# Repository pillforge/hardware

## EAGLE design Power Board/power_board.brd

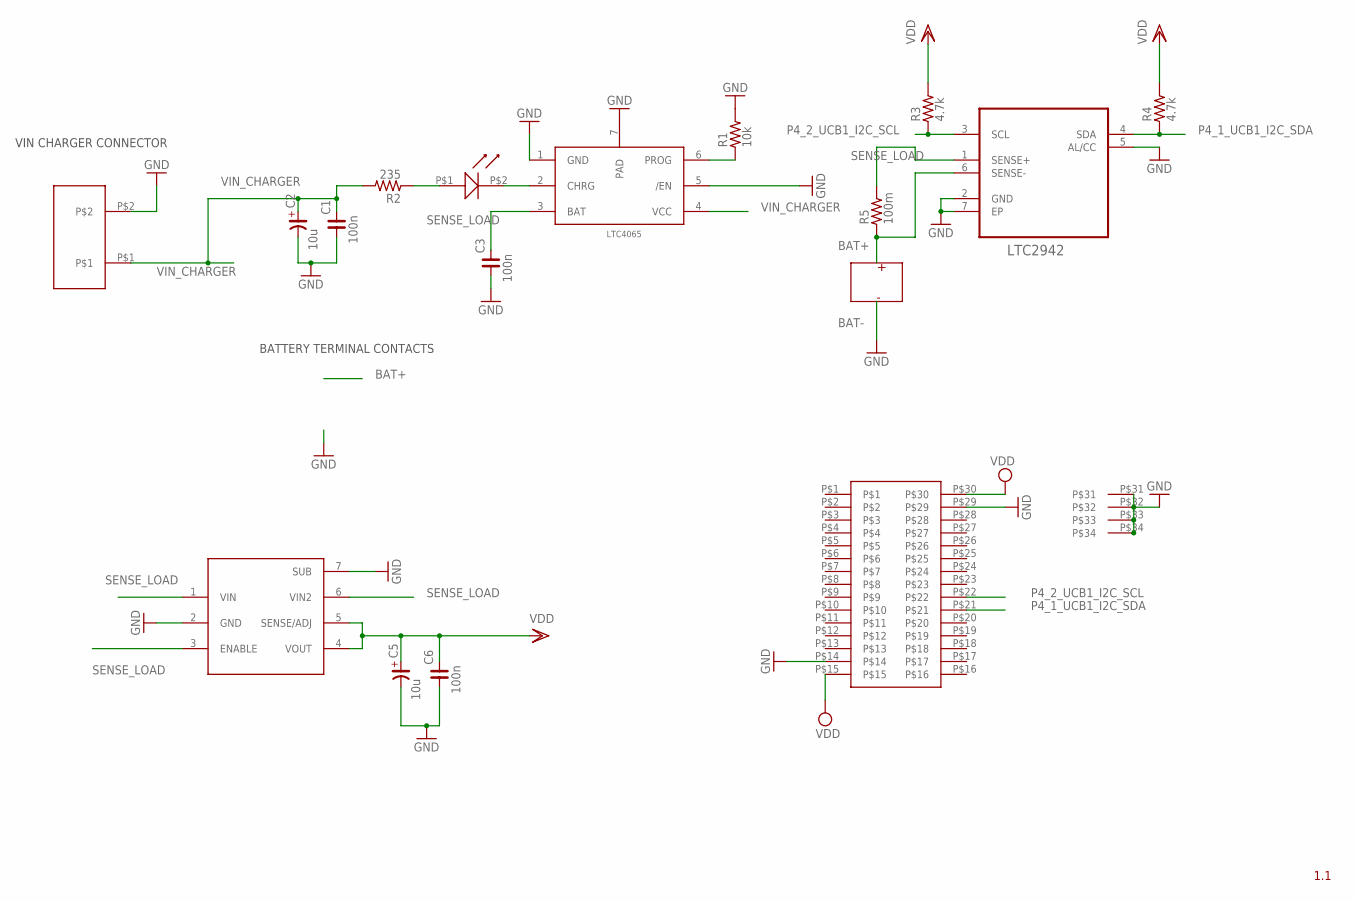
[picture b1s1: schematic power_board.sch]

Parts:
C1, C3, C6: 100n; C0402
C2, C5: 10u; C0402
R1: 10k; R0402
R2: 235; R0402
R3, R4: 4.7k; R0402
R5: 100m; R0402
U1: LTC2942CDCBTRMPBF; DFN200X300X80-7N
U$1: LTC4065
U$2: LED0402; LED_0402
U$3: 55909-0374_PLUG
U$4: NCP606
U$5: ASR_2_REC; ASR_2_CONN

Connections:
BAT+: R5.1, U1.6 (SENSE-)
GND: C1.1, C2.2 (-), C3.1, C5.2 (-), C6.1, R1.2, U1.2 (GND), U1.5 (AL/CC), U1.7 (EP), U$1.1 (GND), U$1.5 (/EN), U$1.7 (PAD), U$3.P$14, U$3.P$29, U$3.P$31, U$3.P$32, U$3.P$33, U$3.P$34, U$4.2 (GND), U$4.7 (SUB), U$5.P$2
unnamed: R1.1, U$1.6 (PROG)
unnamed: R2.1, U$2.P$1 (A)
unnamed: U$1.2 (CHRG), U$2.P$2 (K)
P4_1_UCB1_I2C_SDA: R4.1, U1.4 (SDA), U$3.P$21
P4_2_UCB1_I2C_SCL: R3.1, U1.3 (SCL), U$3.P$22
SENSE_LOAD: C3.2, R5.2, U1.1 (SENSE+), U$1.3 (BAT), U$4.1 (VIN), U$4.3 (ENABLE), U$4.6 (VIN2)
VDD: C5.1 (+), C6.2, R3.2, R4.2, U$3.P$15, U$3.P$30, U$4.4 (VOUT), U$4.5 (SENSE/ADJ)
VIN_CHARGER: C1.2, C2.1 (+), R2.2, U$1.4 (VCC), U$5.P$1

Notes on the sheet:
BAT-
BATTERY TERMINAL CONTACTS
VIN CHARGER CONNECTOR
1.1

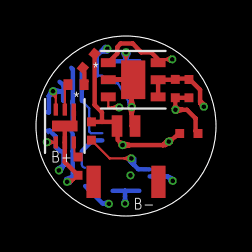
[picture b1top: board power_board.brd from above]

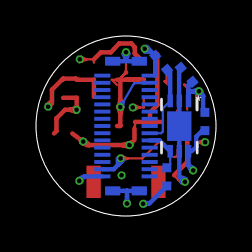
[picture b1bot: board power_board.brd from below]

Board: 4 copper layers, 10.0 x 10.0 mm, 16 parts (6 on the bottom side), 10 nets.

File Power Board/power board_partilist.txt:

Part Value             Device            Package			Vendor										Part Number
C1   100n              C_0402            C0402                                                                                                            
C2   10u               CP_               C0402                                                                                                            
C3   100n              C_0402            C0402                                                                                                            
C5   10u               CP_               C0402                                                                                                            
C6   100n              C_0402            C0402                                                                                                            
R1   10k               R_0402            R0402                                                                                                            
R2   235               R_0402            R0402                                                                                                            
R3   4.7k              R_0402            R0402                                                                                                            
R4   4.7k              R_0402            R0402                                                                                                            
R5   100m              R_0402            R0402                                                                                                            
U$1  LTC4065           LTC4065           LTC4065            DIGI-KEY                                        LTC4065AEDC#TRMPBFCT-ND                                                      
U$2  LED0402           LED0402           LED_0402           DIGI-KEY                                        511-1653-1-ND                                                       
U$3  55909-0374_PLUG   55909-0374_PLUG   55909-0374_PLUG    
U$4  NCP606            NCP606            NCP606             DIGI-KEY                                        NCP606MN33T2GOSCT-ND                                              
U$5  ASR_2_REC         ASR_2_REC         ASR_2_CONN         tlcelectronics.secured-service.com          	BM02B-ASRS-TF(LF)(SN)                                                                      
U1   LTC2942CDCBTRMPBF LTC2942CDCBTRMPBF DFN20        		DIGI-KEY  										LTC2942CDCB#TRMPBFCT-ND

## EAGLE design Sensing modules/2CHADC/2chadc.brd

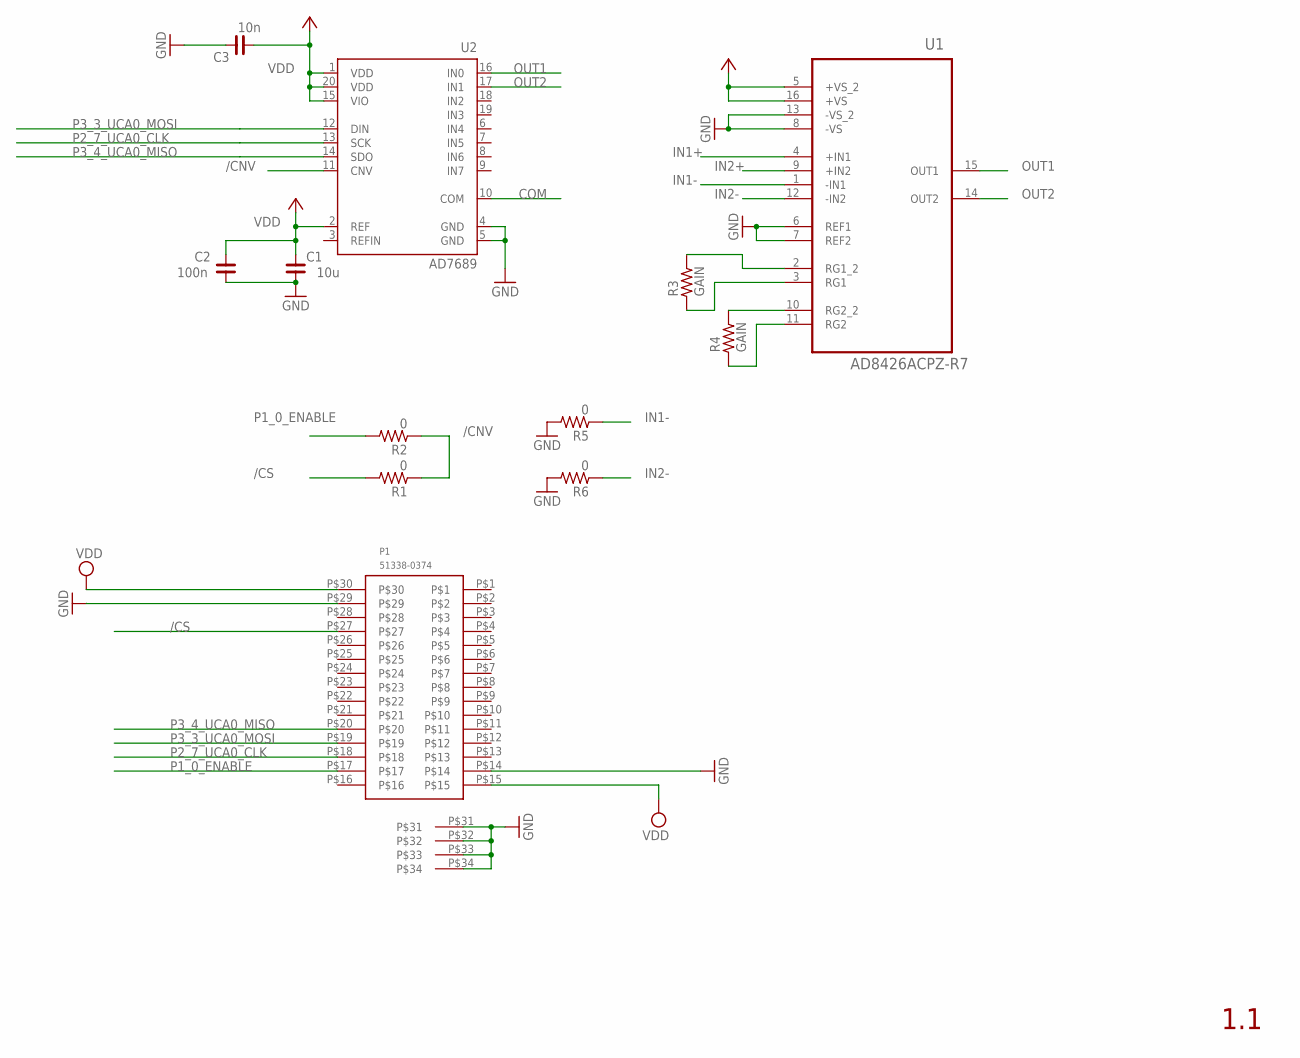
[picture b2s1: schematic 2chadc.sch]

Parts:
C1: 10u; C0402
C2: 100n; C0402
C3: 10n; C0402
P1: 51338-0374; 51338-0374_RECEPTACLE
R1, R2, R5, R6: 0; R0402
R3, R4: GAIN; R0402
U1: AD8426ACPZ-R7; QFN65P400X400X100-16N
U2: AD7689; LFCSP20

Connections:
+3V3: U1.5 (+VS_2), U1.16 (+VS)
/CNV: R1.1, R2.1, U2.11 (CNV)
/CS: P1.P$27, R1.2
COM: U2.10 (COM)
GND: C1.1, C2.1, C3.2, P1.P$14, P1.P$29, P1.P$31, P1.P$32, P1.P$33, P1.P$34, R5.2, R6.2, U1.6 (REF1), U1.7 (REF2), U1.8 (-VS), U1.13 (-VS_2), U2.4 (GND), U2.5 (GND)
IN1+: U1.4 (+IN1)
IN1-: R5.1, U1.1 (-IN1)
IN2+: U1.9 (+IN2)
IN2-: R6.1, U1.12 (-IN2)
unnamed: R4.2, U1.10 (RG2_2)
unnamed: R4.1, U1.11 (RG2)
unnamed: R3.1, U1.3 (RG1)
unnamed: R3.2, U1.2 (RG1_2)
OUT1: U1.15 (OUT1), U2.16 (IN0)
OUT2: U1.14 (OUT2), U2.17 (IN1)
P1_0_ENABLE: P1.P$17, R2.2
P2_7_UCA0_CLK: P1.P$18, U2.13 (SCK)
P3_3_UCA0_MOSI: P1.P$19, U2.12 (DIN)
P3_4_UCA0_MISO: P1.P$20, U2.14 (SDO)
VDD: C1.2, C2.2, C3.1, P1.P$15, P1.P$30, U2.1 (VDD), U2.2 (REF), U2.15 (VIO), U2.20 (VDD)

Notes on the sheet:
1.1

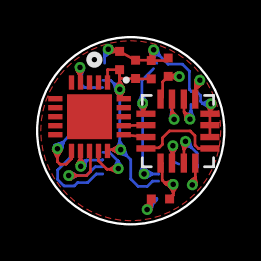
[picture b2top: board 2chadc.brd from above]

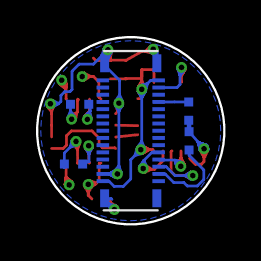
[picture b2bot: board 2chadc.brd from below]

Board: 2 copper layers, 10.4 x 10.4 mm, 12 parts (5 on the bottom side), 17 nets.

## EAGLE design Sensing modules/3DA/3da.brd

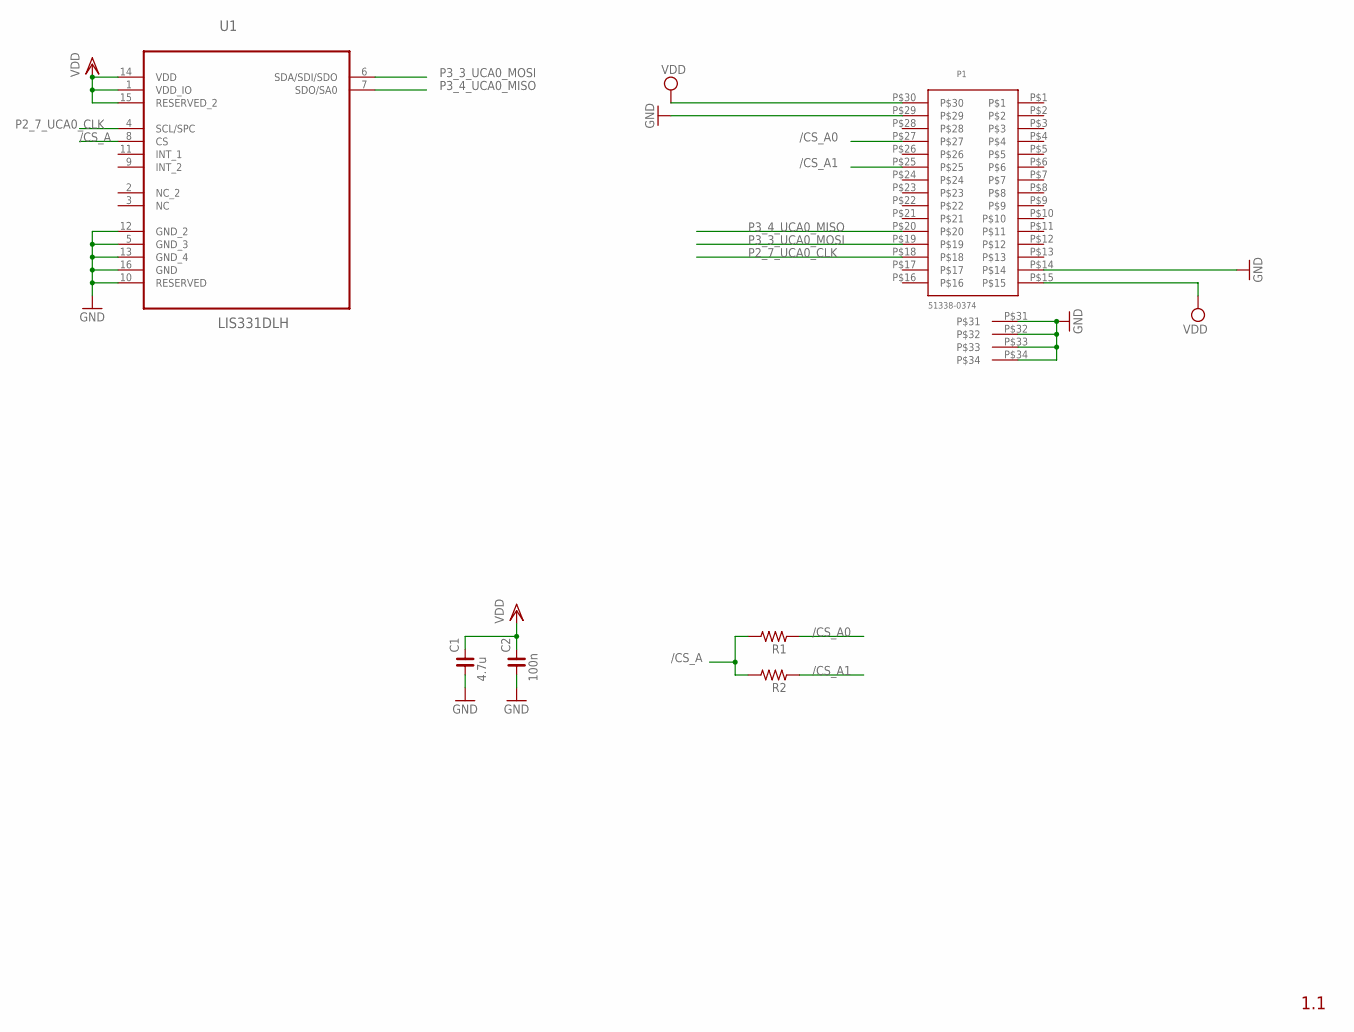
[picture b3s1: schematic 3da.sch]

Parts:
C1: 4.7u; C0402
C2: 100n; C0402
P1: 51338-0374; 51338-0374_RECEPTACLE
R1, R2: R_0402; R0402
U1: LIS331DLH; LGA16R50P3X5_300X300X100

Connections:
/CS_A: R1.2, R2.2, U1.8 (CS)
/CS_A0: P1.P$27, R1.1
/CS_A1: P1.P$25, R2.1
GND: C1.1, C2.1, P1.P$14, P1.P$29, P1.P$31, P1.P$32, P1.P$33, P1.P$34, U1.5 (GND_3), U1.10 (RESERVED), U1.12 (GND_2), U1.13 (GND_4), U1.16 (GND)
P2_7_UCA0_CLK: P1.P$18, U1.4 (SCL/SPC)
P3_3_UCA0_MOSI: P1.P$19, U1.6 (SDA/SDI/SDO)
P3_4_UCA0_MISO: P1.P$20, U1.7 (SDO/SA0)
VDD: C1.2, C2.2, P1.P$15, P1.P$30, U1.1 (VDD_IO), U1.14 (VDD), U1.15 (RESERVED_2)

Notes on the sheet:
1.1

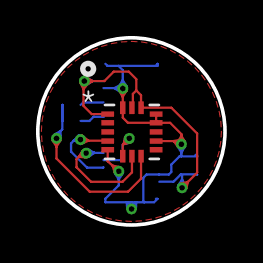
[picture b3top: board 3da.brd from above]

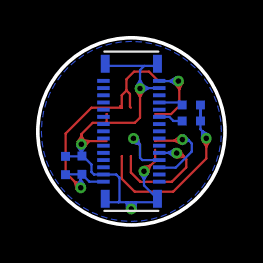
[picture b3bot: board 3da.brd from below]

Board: 2 copper layers, 10.4 x 10.4 mm, 6 parts (5 on the bottom side), 8 nets.

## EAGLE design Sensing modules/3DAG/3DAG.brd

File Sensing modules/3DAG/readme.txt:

XXXXXXXXXXXXXXXXXXXXXXXXXXXXXXXXXXXXXXXXXXXXXXXXXXXXXXXXXXXXXXXXXXXXXXXXXXXXX
X                                                                           X
X   Artwork and documentation done by: STORM LAB                            X
X                                                                           X
X   Company: VANDERBILT UNIVERSITY                                          X
XXXXXXXXXXXXXXXXXXXXXXXXXXXXXXXXXXXXXXXXXXXXXXXXXXXXXXXXXXXXXXXXXXXXXXXXXXXXX

PROJECT : 3DAG
PCB NAME : 3DAG
REVISION: 1.1 
DATE: 4-28-2015

PCB DESCRIPTION: 2 LAYER PCB 0.8 MM NOMINAL THICKNESS FR4
		Dimensions in mil (0.001 inch)
                            DOUBLE SIDE SOLDER MASK,
                            DOUBLE SIDE SILKSCREEN,
                            6 MIL MIN TRACE WIDTH AND 6 MIL MIN ISOLATION
		Dielectric constant for FR4 is 4.5

FILE NAME            		DESCRIPTION                               	FILE TYPE
-------------------------------------------------------------------------------------------
***PCB MANUFACTURING FILES:
3DAG.cmp				LAYER 1 COMPONENT SIDE/POSITIV              EXT. GERBER
3DAG.sol				LAYER 2 Inner layer/POSITIV                 EXT. GERBER

3DAG.stc				SOLDER MASK COMPONENT SIDE/NEGATIVE         EXT. GERBER
3DAG.stl				SOLDER MASK SOLDER SIDE/NEGATIVE            EXT. GERBER

3DAG.plc				SILKSCREEN COMPONENT SIDE/POSITIVE          EXT. GERBER
3DAG.pls				SILKSCREEN SOLDER SIDE/POSITIVE             EXT. GERBER

3DAG.crc				SOLDER PAST COMPONENT SIDE/POSITIVE         EXT. GERBER
3DAG.crs				SOLDER PAST SOLDER SIDE/POSITIVE            EXT. GERBER

3DAG.drd				DRILL/MECHANICAL DRAWING                    EXT. GERBER
3DAG.dri				DRILL/NC DRILL REPORT                       ASCII
3DAG.dim				BOARD OUTLINE                      			EXT. GERBER

3DAG_partlist.xls		PART LIST									ASCII

***PDF FILES:
3DAG.PDF	Circuit Diagram

***EAGLE  FILES:
3DAG.SCH			Eagle 6.6 Schematic file
3DAG.BRD			Eagle 6.6 Layout file

README.TXT              THIS FILE                                   ASCII

***REVISION HISTORY

none

END.

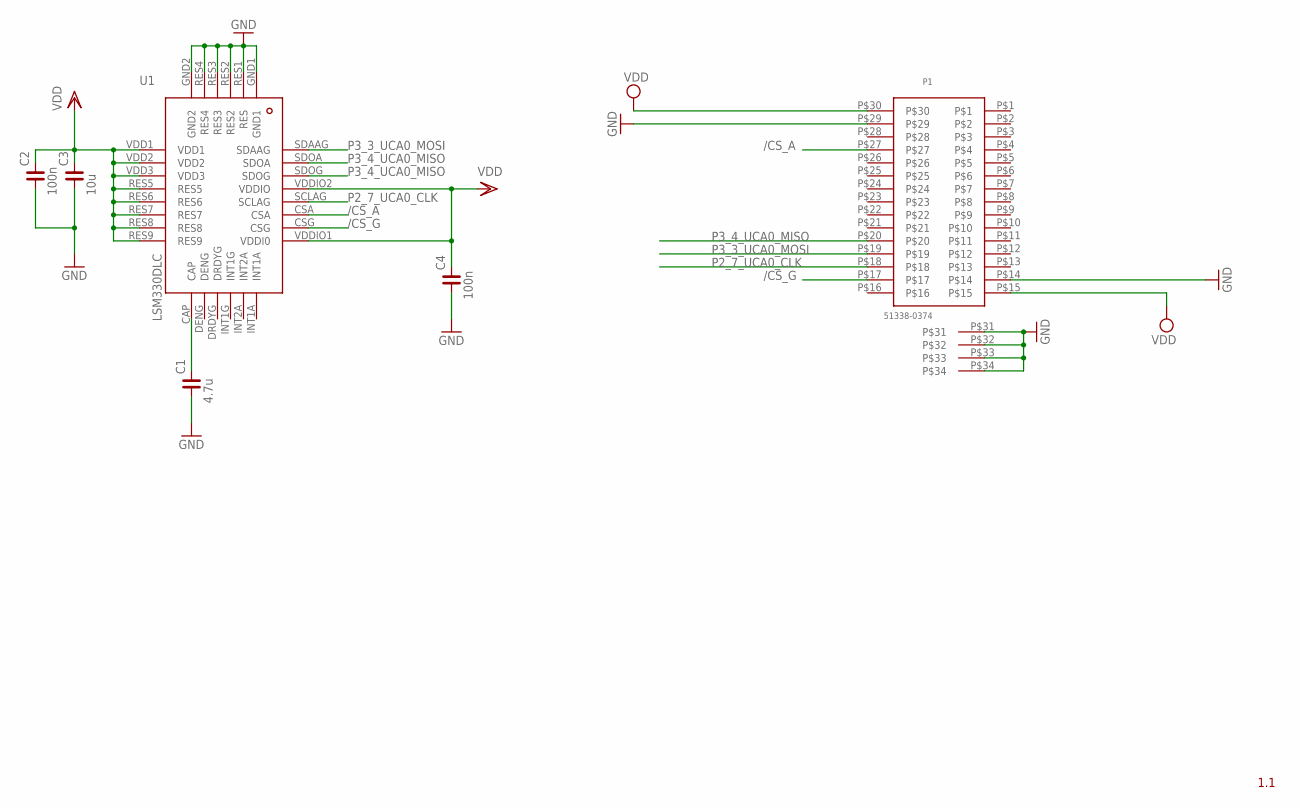
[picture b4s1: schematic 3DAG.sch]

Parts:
C1: 4.7u; C0402
C2, C4: 100n; C0402
C3: 10u; C0402
P1: 51338-0374; 51338-0374_RECEPTACLE
U$4: LSM330DLC

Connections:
/CS_A: P1.P$27, U$4.CSA
/CS_G: P1.P$17, U$4.CSG
GND: C1.1, C2.1, C3.1, C4.1, P1.P$14, P1.P$29, P1.P$31, P1.P$32, P1.P$33, P1.P$34, U$4.GND1, U$4.GND2, U$4.RES1 (RES), U$4.RES2, U$4.RES3, U$4.RES4
unnamed: C1.2, U$4.CAP
P2_7_UCA0_CLK: P1.P$18, U$4.SCLAG
P3_3_UCA0_MOSI: P1.P$19, U$4.SDAAG
P3_4_UCA0_MISO: P1.P$20, U$4.SDOA, U$4.SDOG
VDD: C2.2, C3.2, C4.2, P1.P$15, P1.P$30, U$4.RES5, U$4.RES6, U$4.RES7, U$4.RES8, U$4.RES9, U$4.VDD1, U$4.VDD2, U$4.VDD3, U$4.VDDIO1 (VDDI0), U$4.VDDIO2 (VDDIO)

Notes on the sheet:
1.1

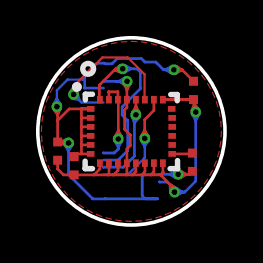
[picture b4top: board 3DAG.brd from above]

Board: 2 copper layers, 10.4 x 10.4 mm, 6 parts (1 on the bottom side), 8 nets.

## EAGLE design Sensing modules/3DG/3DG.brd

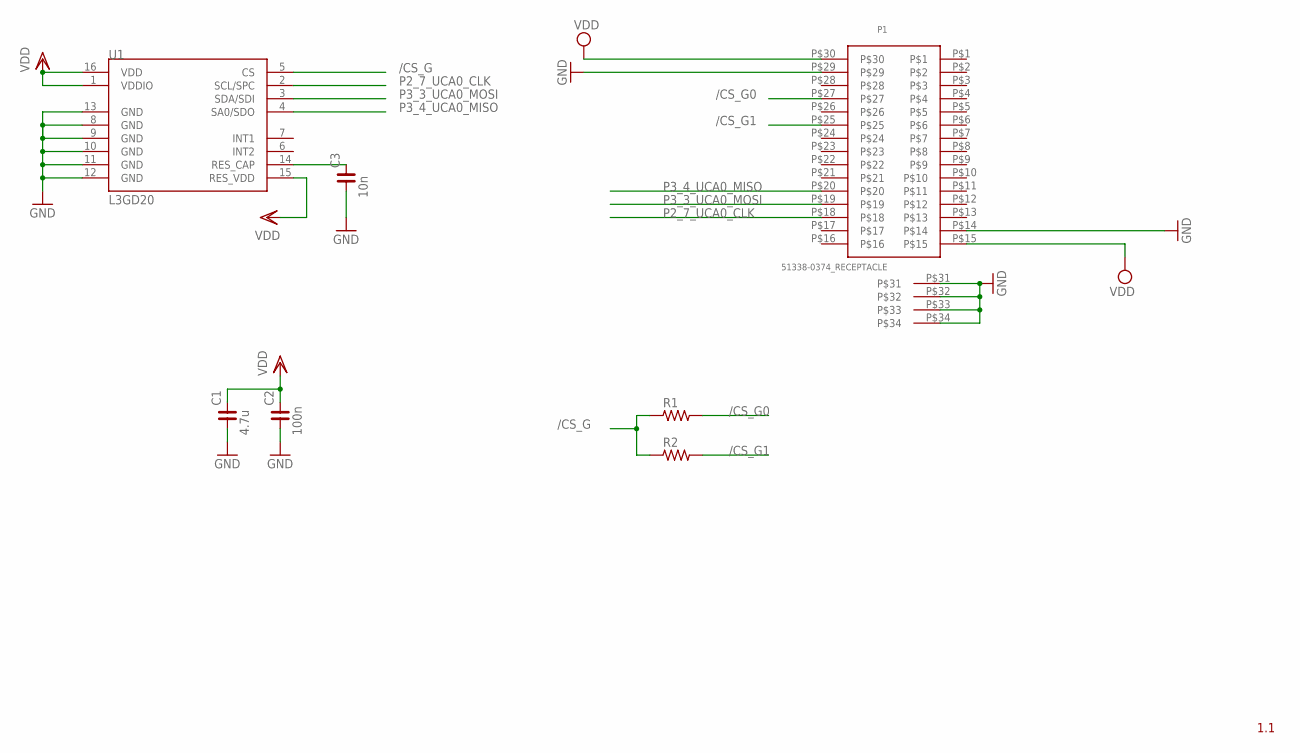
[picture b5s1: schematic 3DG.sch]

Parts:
C1: 4.7u; C0402
C2: 100n; C0402
C3: 10n; C0402
P1: 51338-0374_RECEPTACLE
R1, R2: R_0402; R0402
U1: L3GD20; LGA16-4X4

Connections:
/CS_G: R1.1, R2.1, U1.5 (CS)
/CS_G0: P1.P$27, R1.2
/CS_G1: P1.P$25, R2.2
GND: C1.1, C2.1, C3.1, P1.P$14, P1.P$29, P1.P$31, P1.P$32, P1.P$33, P1.P$34, U1.8 (GND), U1.9 (GND), U1.10 (GND), U1.11 (GND), U1.12 (GND), U1.13 (GND)
unnamed: C3.2, U1.14 (RES_CAP)
P2_7_UCA0_CLK: P1.P$18, U1.2 (SCL/SPC)
P3_3_UCA0_MOSI: P1.P$19, U1.3 (SDA/SDI)
P3_4_UCA0_MISO: P1.P$20, U1.4 (SA0/SDO)
VDD: C1.2, C2.2, P1.P$15, P1.P$30, U1.1 (VDDIO), U1.15 (RES_VDD), U1.16 (VDD)

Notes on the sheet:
1.1

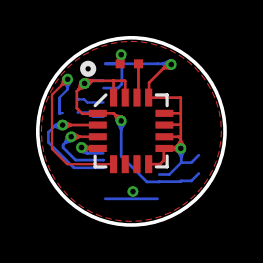
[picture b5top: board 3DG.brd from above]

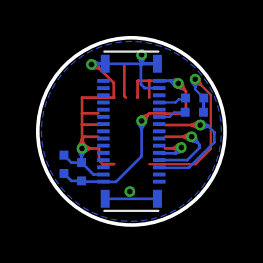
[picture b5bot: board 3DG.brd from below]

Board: 2 copper layers, 10.4 x 10.4 mm, 7 parts (5 on the bottom side), 9 nets.

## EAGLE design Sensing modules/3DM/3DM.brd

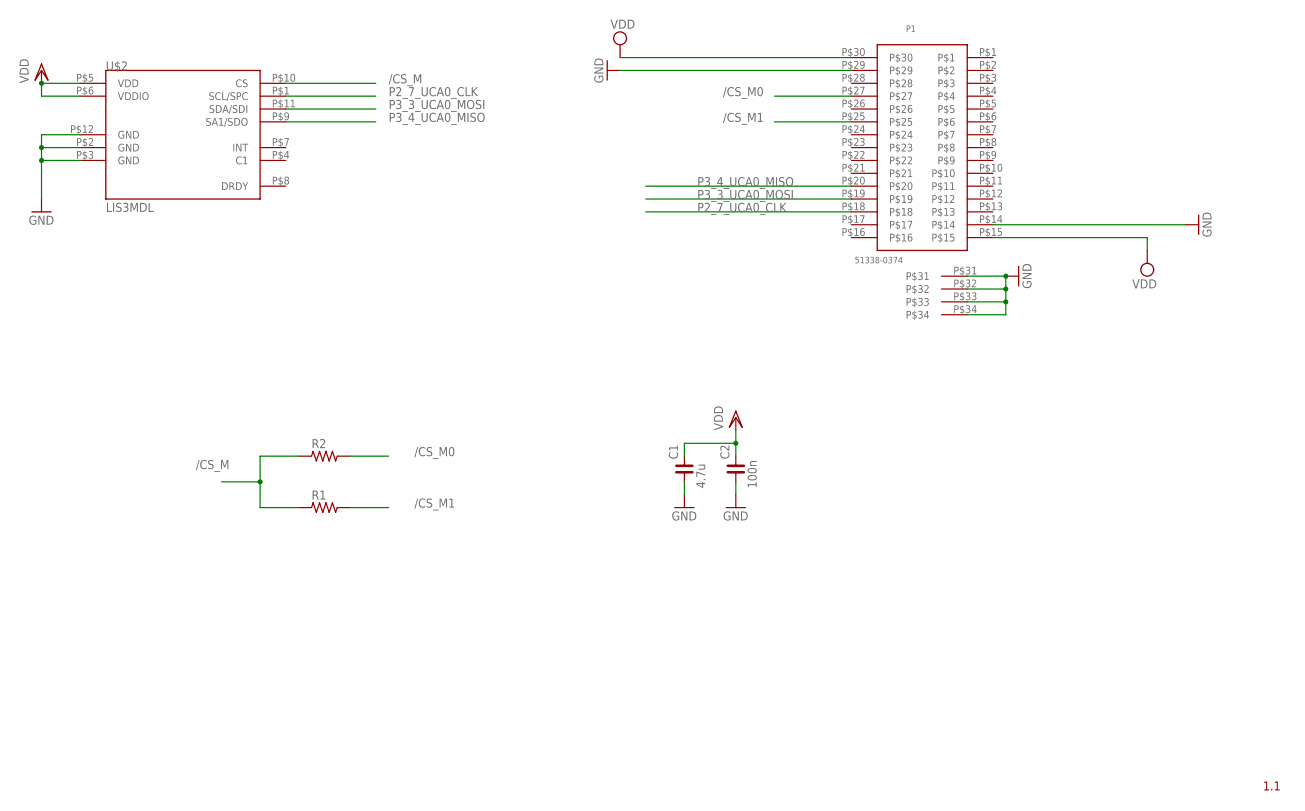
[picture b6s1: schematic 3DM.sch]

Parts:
C1: 4.7u; C0402
C2: 100n; C0402
P1: 51338-0374; 51338-0374_RECEPTACLE
R1, R2: R_0402; R0402
U$2: LIS3MDL; VFLGA-2X2X1

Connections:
/CS_M: R1.1, R2.1, U$2.P$10 (CS)
/CS_M0: P1.P$27, R2.2
/CS_M1: P1.P$25, R1.2
GND: C1.1, C2.1, P1.P$14, P1.P$29, P1.P$31, P1.P$32, P1.P$33, P1.P$34, U$2.P$2 (GND), U$2.P$3 (GND), U$2.P$12 (GND)
P2_7_UCA0_CLK: P1.P$18, U$2.P$1 (SCL/SPC)
P3_3_UCA0_MOSI: P1.P$19, U$2.P$11 (SDA/SDI)
P3_4_UCA0_MISO: P1.P$20, U$2.P$9 (SA1/SDO)
VDD: C1.2, C2.2, P1.P$15, P1.P$30, U$2.P$5 (VDD), U$2.P$6 (VDDIO)

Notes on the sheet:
1.1

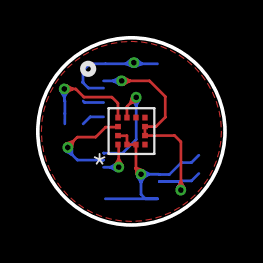
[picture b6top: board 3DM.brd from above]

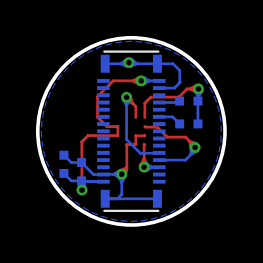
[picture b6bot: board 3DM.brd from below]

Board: 2 copper layers, 10.4 x 10.4 mm, 6 parts (5 on the bottom side), 8 nets.

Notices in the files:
parts and their libraries:
rc-master-smd: Copyright (C) 2007, Bob Starr
SparkFun-Sensors: Licensing: Creative Commons ShareAlike 4.0 International - https://creativecommons.org/licenses/by-sa/4.0
